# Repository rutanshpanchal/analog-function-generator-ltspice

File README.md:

# analog-function-generator-ltspice
Analog function generator capable of generating sine, square, triangle, and sawtooth waveforms using LM741 op-amps designed and simulated in LTspice.
### 3D PCB Design

---

### KiCAD Routing

---

### LTspice Circuit

---

### LTspice Output Waveform

---

### PCB Schematic

## 📈 Simulation Files
The LTspice simulation files for the analog function generator are available in the `/simulation` folder.

### Included Files
- Function generator LTspice schematic (`.asc`)
- Simulation outputs
- Circuit waveform analysis

  ---

## 🎥 Project Demonstration Video

Watch the working demonstration here:

[▶️ Watch Demo Video 1](./output_1.mp4)
[▶️ Watch Demo Video 2](./output_2.mp4)

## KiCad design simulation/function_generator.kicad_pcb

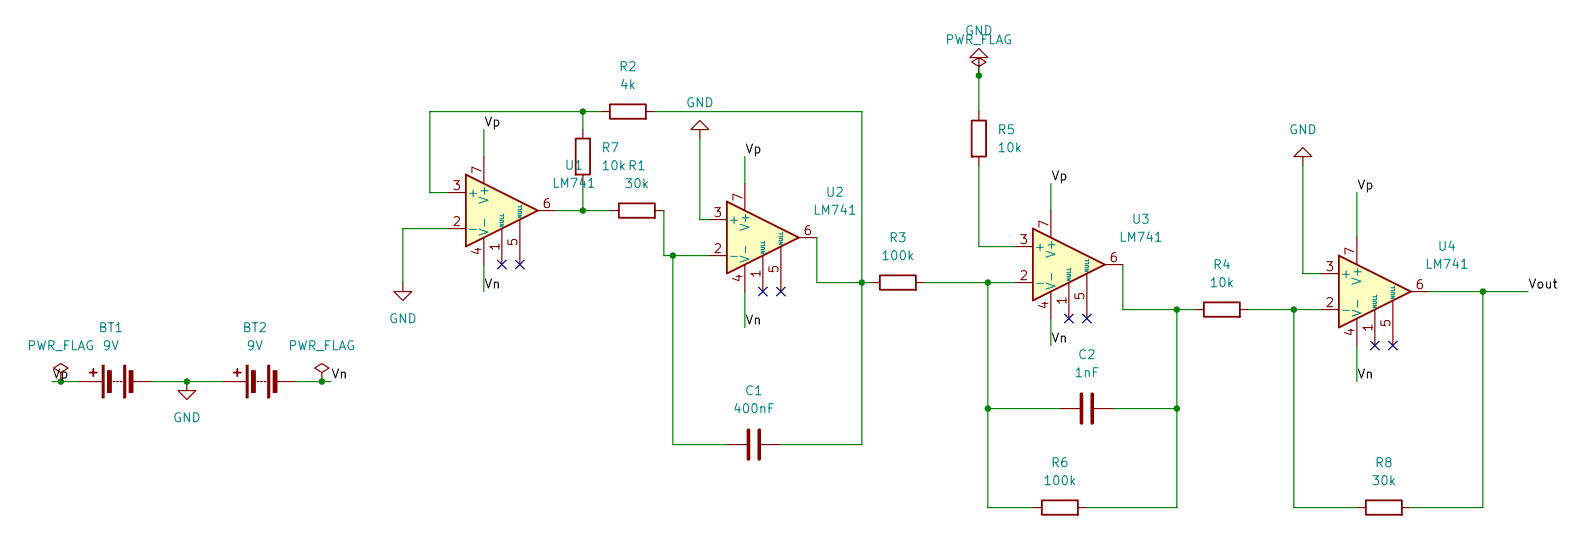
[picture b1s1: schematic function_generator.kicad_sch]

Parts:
BT1, BT2: 9V; PinHeader_1x02_P2.54mm_Vertical_SMD_Pin1Left
C1: 400nF; C_Disc_D5.0mm_W2.5mm_P2.50mm
C2: 1nF; C_Disc_D5.0mm_W2.5mm_P2.50mm
R1, R8: 30k; R_Axial_DIN0207_L6.3mm_D2.5mm_P7.62mm_Horizontal
R2: 4k; R_Axial_DIN0207_L6.3mm_D2.5mm_P7.62mm_Horizontal
R3, R6: 100k; R_Axial_DIN0207_L6.3mm_D2.5mm_P7.62mm_Horizontal
R4, R5, R7: 10k; R_Axial_DIN0207_L6.3mm_D2.5mm_P7.62mm_Horizontal
U1, U2, U3, U4: LM741; DIP-8_W7.62mm

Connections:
/Vn: BT2.2 (-), U1.4 (V-), U2.4 (V-), U3.4 (V-), U4.4 (V-)
/Vout: R8.2, U4.6
/Vp: BT1.1 (+), U1.7 (V+), U2.7 (V+), U3.7 (V+), U4.7 (V+)
GND: BT1.2 (-), BT2.1 (+), R5.1, U1.2 (-), U2.3 (+), U4.3 (+)
unnamed: C1.2, R2.2, R3.1, U2.6
unnamed: C2.2, R4.1, R6.2, U3.6
unnamed: R1.1, R7.2, U1.6
unnamed: R2.1, R7.1, U1.3 (+)
unnamed: C1.1, R1.2, U2.2 (-)
unnamed: R5.2, U3.3 (+)
unnamed: C2.1, R3.2, R6.1, U3.2 (-)
unnamed: R4.2, R8.1, U4.2 (-)

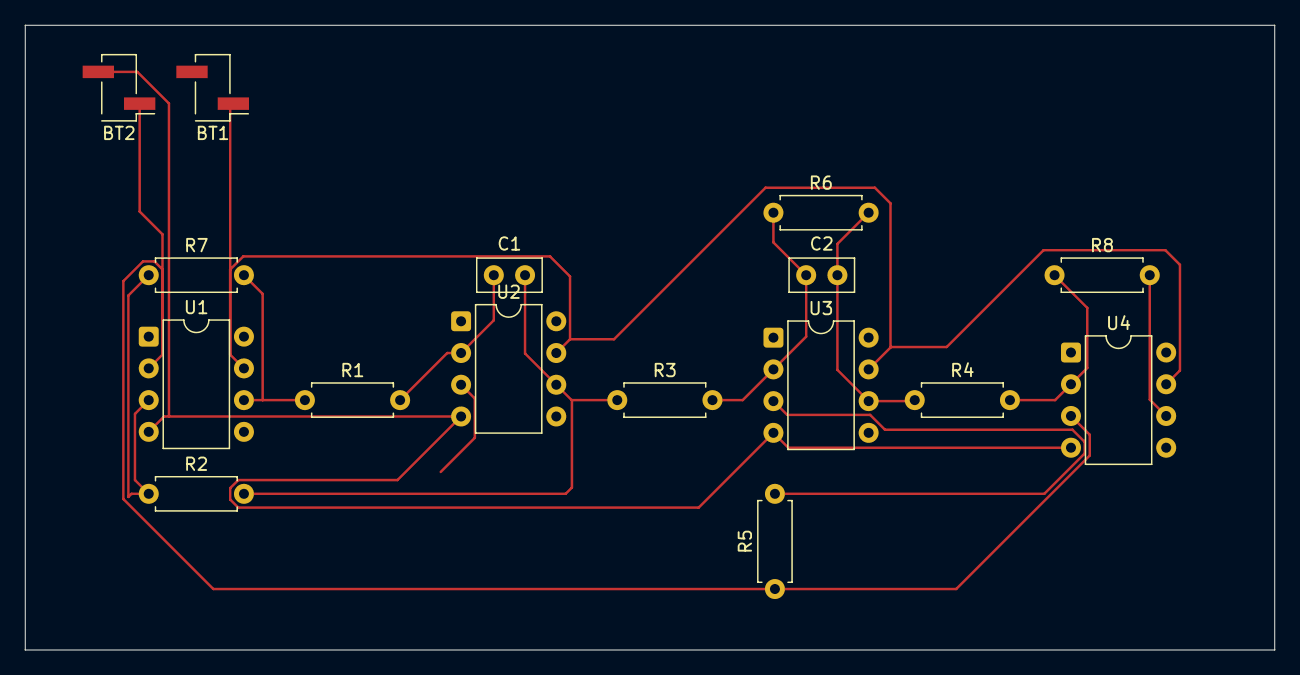
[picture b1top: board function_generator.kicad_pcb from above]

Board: 2 copper layers, 100.0 x 50.0 mm, 16 parts (0 on the bottom side), 12 nets.

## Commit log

2026-05-19 Add image files directory for project assets
2026-05-19 Create simulation
2026-05-19 Create circuit
2026-05-19 Create docs
2026-05-19 Add README for project images
